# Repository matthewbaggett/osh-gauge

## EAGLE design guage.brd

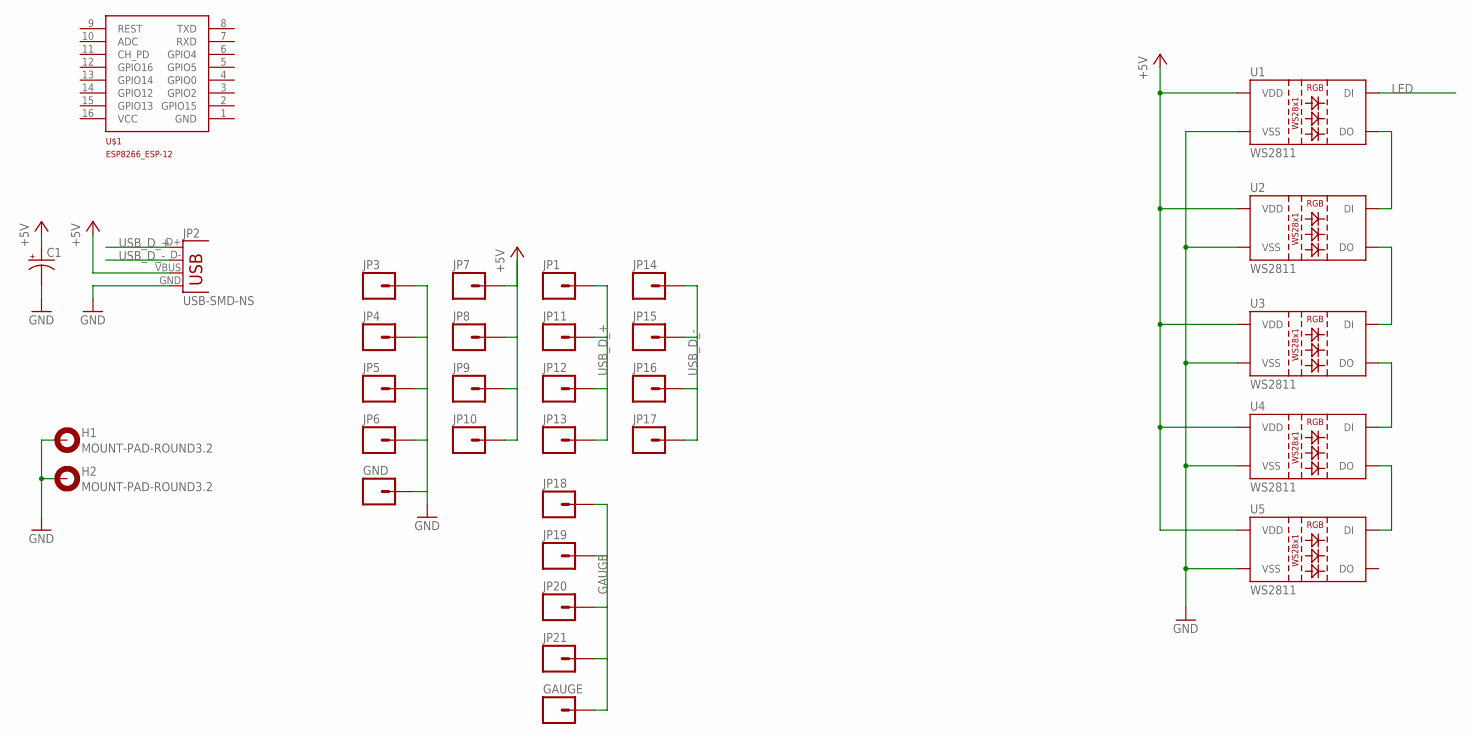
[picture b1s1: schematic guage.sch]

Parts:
C1: 100UF-25V-20%(PTH); CPOL-RADIAL-100UF-25V
GAUGE: M01OFFSET; 1X01_OFFSET
GND: M01OFFSET; 1X01_OFFSET
H1, H2: MOUNT-PAD-ROUND3.2; 3,2-PAD
JP1, JP3, JP4, JP5, JP6, JP7, JP8, JP9, JP10, JP11, JP12, JP13, JP14, JP15, JP16, JP17, JP18, JP19, JP20, JP21: M01SMD-4.5X1.5; PAD-1.5X4.5
JP2: USB-SMD-NS; USB-MINIB-NOSTOP
U1, U2, U3, U4, U5: WS2811; LED-TRICOLOR-5050-IC
U$1: ESP8266_ESP-12; ESP8266-ESP12

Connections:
+5V: C1.1 (+), JP2.VBUS, JP7.P$1, JP8.P$1, JP9.P$1, JP10.P$1, U1.3 (VDD), U1.5 (VDD), U2.3 (VDD), U2.5 (VDD), U3.3 (VDD), U3.5 (VDD), U4.3 (VDD), U4.5 (VDD), U5.3 (VDD), U5.5 (VDD)
GAUGE: GAUGE.1, JP18.P$1, JP19.P$1, JP20.P$1, JP21.P$1
GND: C1.2 (-), GND.1, H1.B3,2, H2.B3,2, JP2.GND, JP3.P$1, JP4.P$1, JP5.P$1, JP6.P$1, U1.6 (VSS), U2.6 (VSS), U3.6 (VSS), U4.6 (VSS), U5.6 (VSS)
LED: U1.2 (DI)
unnamed: U1.1 (DO), U2.2 (DI)
unnamed: U2.1 (DO), U3.2 (DI)
unnamed: U3.1 (DO), U4.2 (DI)
unnamed: U4.1 (DO), U5.2 (DI)
USB_D_+: JP1.P$1, JP2.D+, JP11.P$1, JP12.P$1, JP13.P$1
USB_D_-: JP2.D-, JP14.P$1, JP15.P$1, JP16.P$1, JP17.P$1

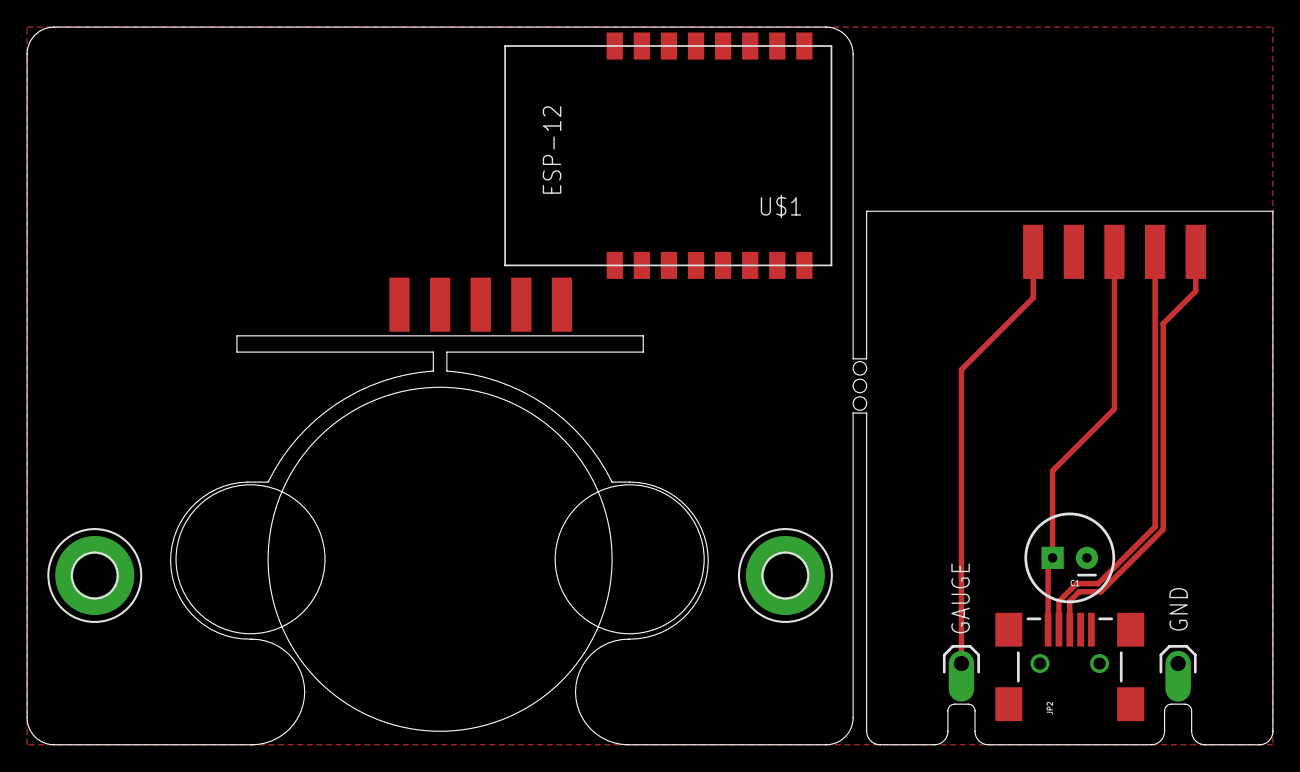
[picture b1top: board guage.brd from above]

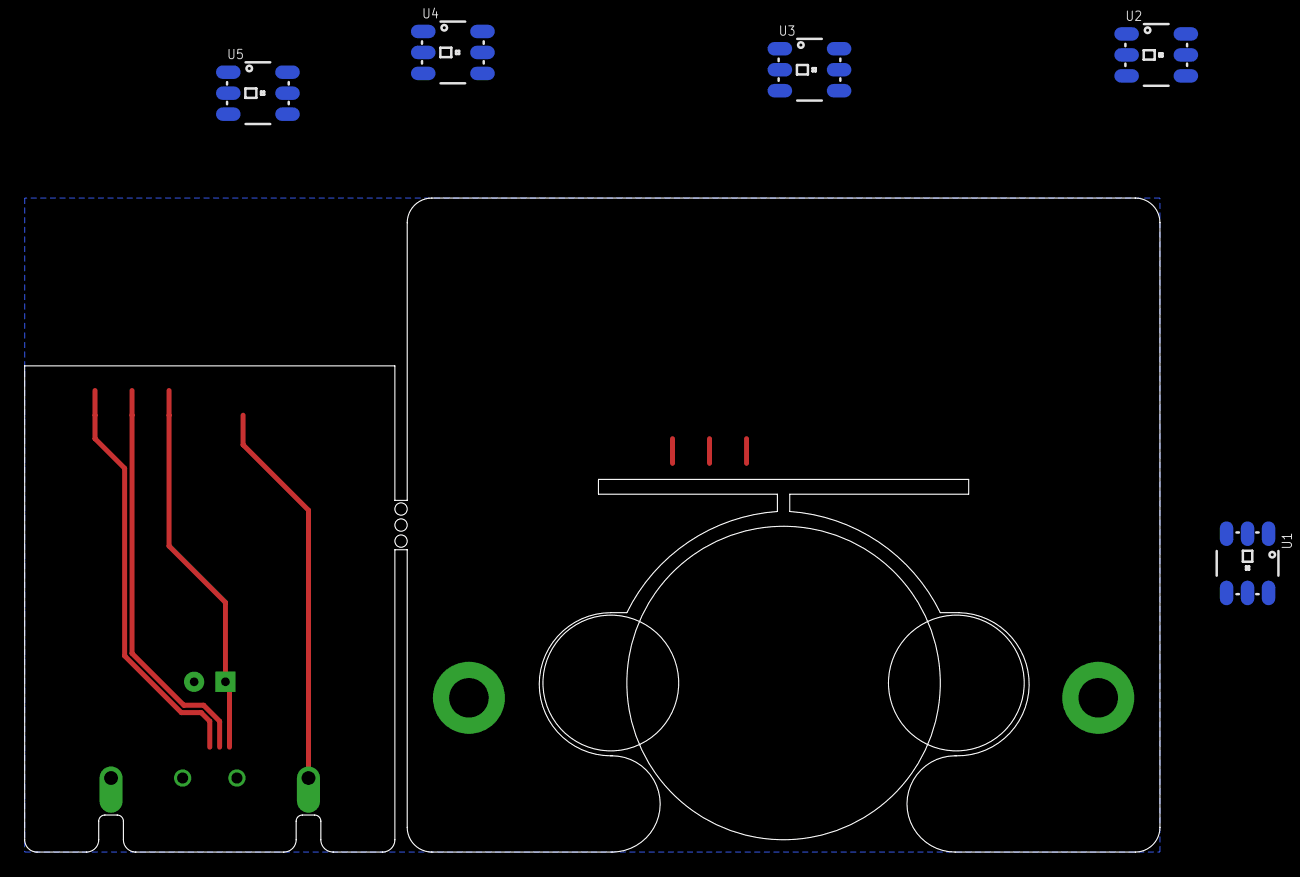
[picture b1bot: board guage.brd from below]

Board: 2 copper layers, 92.0 x 53.0 mm, 32 parts (5 on the bottom side), 9 nets.

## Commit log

2016-11-03 Initial commit from last night
2016-11-03 I can't spell
2016-11-03 initial export images of board & schem

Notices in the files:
parts and their libraries:
SparkFun-Connectors: Licensing: Creative Commons ShareAlike 4.0 International - https://creativecommons.org/licenses/by-sa/4.0
